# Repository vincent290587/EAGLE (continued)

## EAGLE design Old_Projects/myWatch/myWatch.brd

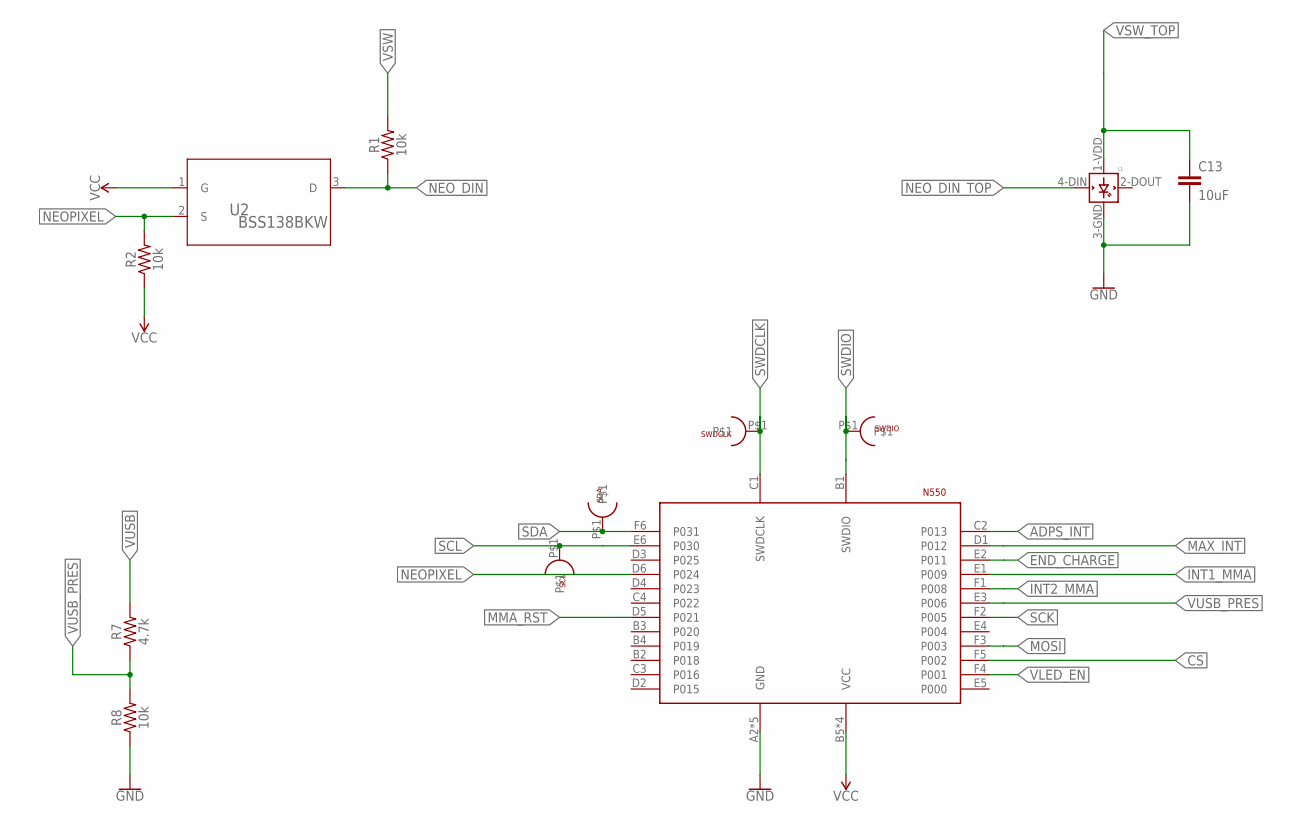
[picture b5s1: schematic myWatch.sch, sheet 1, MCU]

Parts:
C13: 10uF; 0603
L1: WS2812B
R1, R2, R8: 10k; 0603
R7: 4.7k; 0603
SCL: SCL; TESTPOINT
SDA: SDA; TESTPOINT
SWDCLK: TESTPOINT
SWDIO: TESTPOINT
U2: BSS138BKW; SOT65P210X110-3N
U$1: N5150

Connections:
ADPS_INT: U$1.C2 (P013); also elsewhere on the board
CS: U$1.F5 (P002); also elsewhere on the board
END_CHARGE: U$1.E2 (P011); also elsewhere on the board
GND: C13.2, L1.3-GND (GND), R8.1, U$1.A2 (GND), U$1.A3 (GND), U$1.A4 (GND), U$1.A5 (GND), U$1.A6 (GND); also elsewhere on the board
INT1_MMA: U$1.E1 (P009); also elsewhere on the board
INT2_MMA: U$1.F1 (P008); also elsewhere on the board
MAX_INT: U$1.D1 (P012); also elsewhere on the board
MMA_RST: U$1.D5 (P021); also elsewhere on the board
MOSI: U$1.F3 (P003); also elsewhere on the board
NEOPIXEL: R2.2, U2.2 (S), U$1.D6 (P024)
NEO_DIN: R1.1, U2.3 (D); also elsewhere on the board
NEO_DIN_TOP: L1.4-DIN (DIN); also elsewhere on the board
SCK: U$1.F2 (P005); also elsewhere on the board
SCL: SCL.P$1, U$1.E6 (P030); also elsewhere on the board
SDA: SDA.P$1, U$1.F6 (P031); also elsewhere on the board
SWDCLK: SWDCLK.P$1, U$1.C1 (SWDCLK); also elsewhere on the board
SWDIO: SWDIO.P$1, U$1.B1 (SWDIO); also elsewhere on the board
VCC: R2.1, U2.1 (G), U$1.B5 (VCC), U$1.B6 (VCC), U$1.C5 (VCC), U$1.C6 (VCC); also elsewhere on the board
VLED_EN: U$1.F4 (P001); also elsewhere on the board
VSW: R1.2; also elsewhere on the board
VSW_TOP: C13.1, L1.1-VDD (VDD); also elsewhere on the board
VUSB: R7.2; also elsewhere on the board
VUSB_PRES: R7.1, R8.2, U$1.E3 (P006)

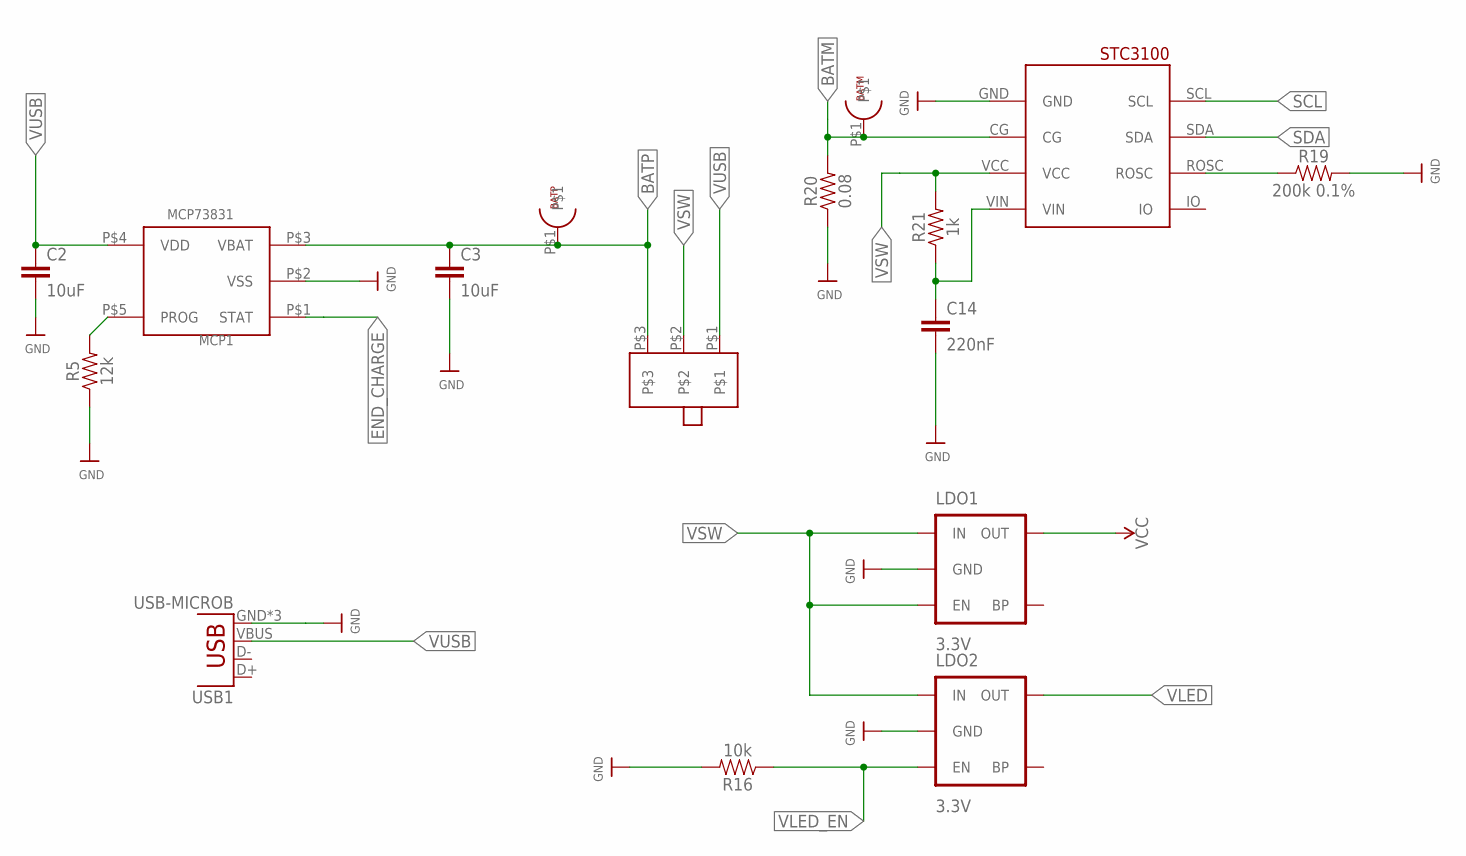
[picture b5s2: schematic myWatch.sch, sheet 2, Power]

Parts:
BATM: BATM; TESTPOINT
BATP: BATP; TESTPOINT
C2, C3: 10uF; 0603
C14: 220nF; 0603
LDO1, LDO2: 3.3V; SOT23-5
MCP1: MCP73831; 5PIN_SOT23
R5: 12k; 0603
R16: 10k; 0603
R19: 200k 0.1%; 0603
R20: 0.08; 0603
R21: 1k; 0603
STC1: STC3100
U$10: JS102011SAQN
USB1: USB-MICROB

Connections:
BATM: BATM.P$1, R20.2, STC1.CG
BATP: BATP.P$1, C3.1, MCP1.P$3 (VBAT), U$10.P$3
END_CHARGE: MCP1.P$1 (STAT); also elsewhere on the board
GND: C2.2, C3.2, C14.2, LDO1.2 (GND), LDO2.2 (GND), MCP1.P$2 (VSS), R5.1, R16.2, R19.2, R20.1, STC1.GND, USB1.GND, USB1.MT1 (GND), USB1.MT2 (GND); also elsewhere on the board
unnamed: MCP1.P$5 (PROG), R5.2
unnamed: R19.1, STC1.ROSC
unnamed: C14.1, R21.1, STC1.VIN
SCL: STC1.SCL; also elsewhere on the board
SDA: STC1.SDA; also elsewhere on the board
VCC: LDO1.5 (OUT); also elsewhere on the board
VLED: LDO2.5 (OUT); also elsewhere on the board
VLED_EN: LDO2.3 (EN), R16.1; also elsewhere on the board
VSW: LDO1.1 (IN), LDO1.3 (EN), LDO2.1 (IN), R21.2, STC1.VCC, U$10.P$2; also elsewhere on the board
VUSB: C2.1, MCP1.P$4 (VDD), U$10.P$1, USB1.VBUS; also elsewhere on the board

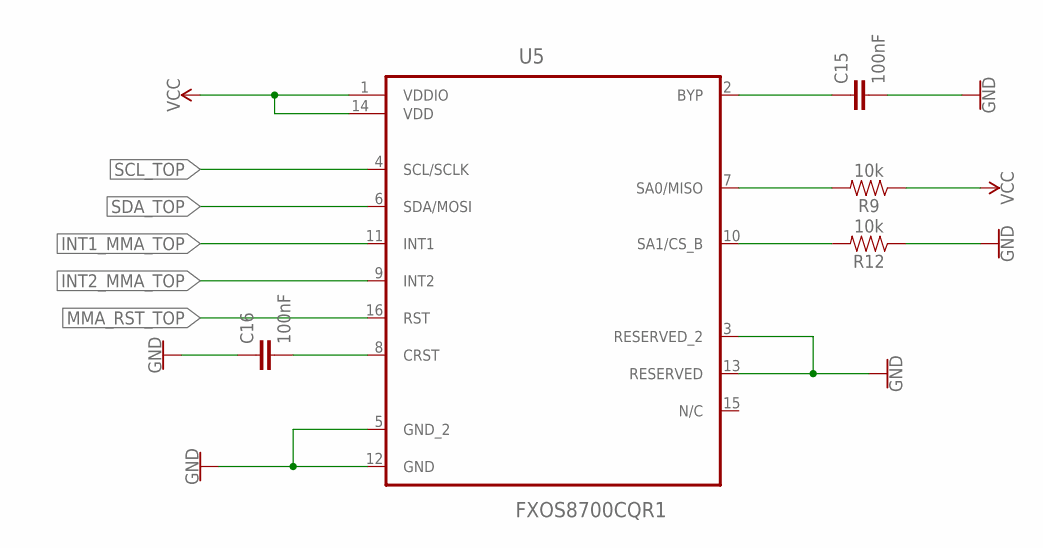
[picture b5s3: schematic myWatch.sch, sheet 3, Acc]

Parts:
C15, C16: 100nF; 0603
R9, R12: 10k; 0603
U5: FXOS8700CQR1; QFN50P300X300X120-16N

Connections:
GND: C15.2, C16.1, R12.1, U5.3 (RESERVED_2), U5.5 (GND_2), U5.12 (GND), U5.13 (RESERVED); also elsewhere on the board
INT1_MMA_TOP: U5.11 (INT1); also elsewhere on the board
INT2_MMA_TOP: U5.9 (INT2); also elsewhere on the board
MMA_RST_TOP: U5.16 (RST); also elsewhere on the board
unnamed: C16.2, U5.8 (CRST)
unnamed: R12.2, U5.10 (SA1/CS_B)
unnamed: R9.2, U5.7 (SA0/MISO)
unnamed: C15.1, U5.2 (BYP)
SCL_TOP: U5.4 (SCL/SCLK); also elsewhere on the board
SDA_TOP: U5.6 (SDA/MOSI); also elsewhere on the board
VCC: R9.1, U5.1 (VDDIO), U5.14 (VDD); also elsewhere on the board

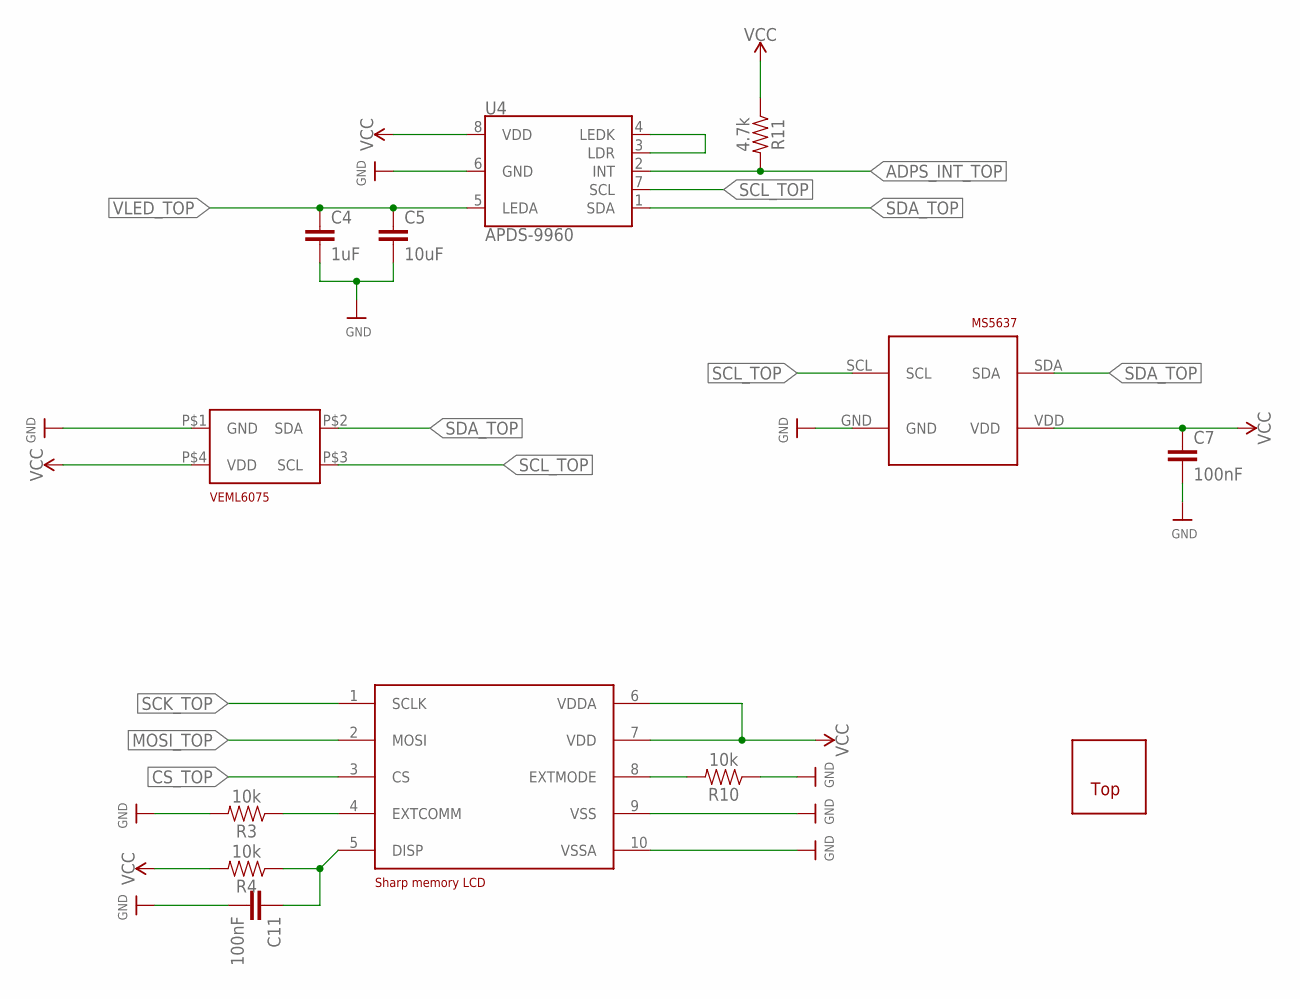
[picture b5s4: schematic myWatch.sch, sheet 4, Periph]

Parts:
C4: 1uF; 0603
C5: 10uF; 0603
C7, C11: 100nF; 0603
MS5637: MS5637
R3, R4, R10: 10k; 0603
R11: 4.7k; 0603
SHARP: SHARP27
U4: APDS-9960
U$2: VEML6075
U$6: WATCH1; WATCH

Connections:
ADPS_INT_TOP: R11.2, U4.2 (INT); also elsewhere on the board
CS_TOP: SHARP.3 (CS); also elsewhere on the board
GND: C4.2, C5.2, C7.2, C11.2, MS5637.GND, R3.2, R10.1, SHARP.9 (VSS), SHARP.10 (VSSA), U4.6 (GND), U$2.P$1 (GND); also elsewhere on the board
MOSI_TOP: SHARP.2 (MOSI); also elsewhere on the board
unnamed: U4.3 (LDR), U4.4 (LEDK)
unnamed: R10.2, SHARP.8 (EXTMODE)
unnamed: R3.1, SHARP.4 (EXTCOMM)
unnamed: C11.1, R4.1, SHARP.5 (DISP)
SCK_TOP: SHARP.1 (SCLK); also elsewhere on the board
SCL_TOP: MS5637.SCL, U4.7 (SCL), U$2.P$3 (SCL); also elsewhere on the board
SDA_TOP: MS5637.SDA, U4.1 (SDA), U$2.P$2 (SDA); also elsewhere on the board
VCC: C7.1, MS5637.VDD, R4.2, R11.1, SHARP.6 (VDDA), SHARP.7 (VDD), U4.8 (VDD), U$2.P$4 (VDD); also elsewhere on the board
VLED_TOP: C4.1, C5.1, U4.5 (LEDA); also elsewhere on the board

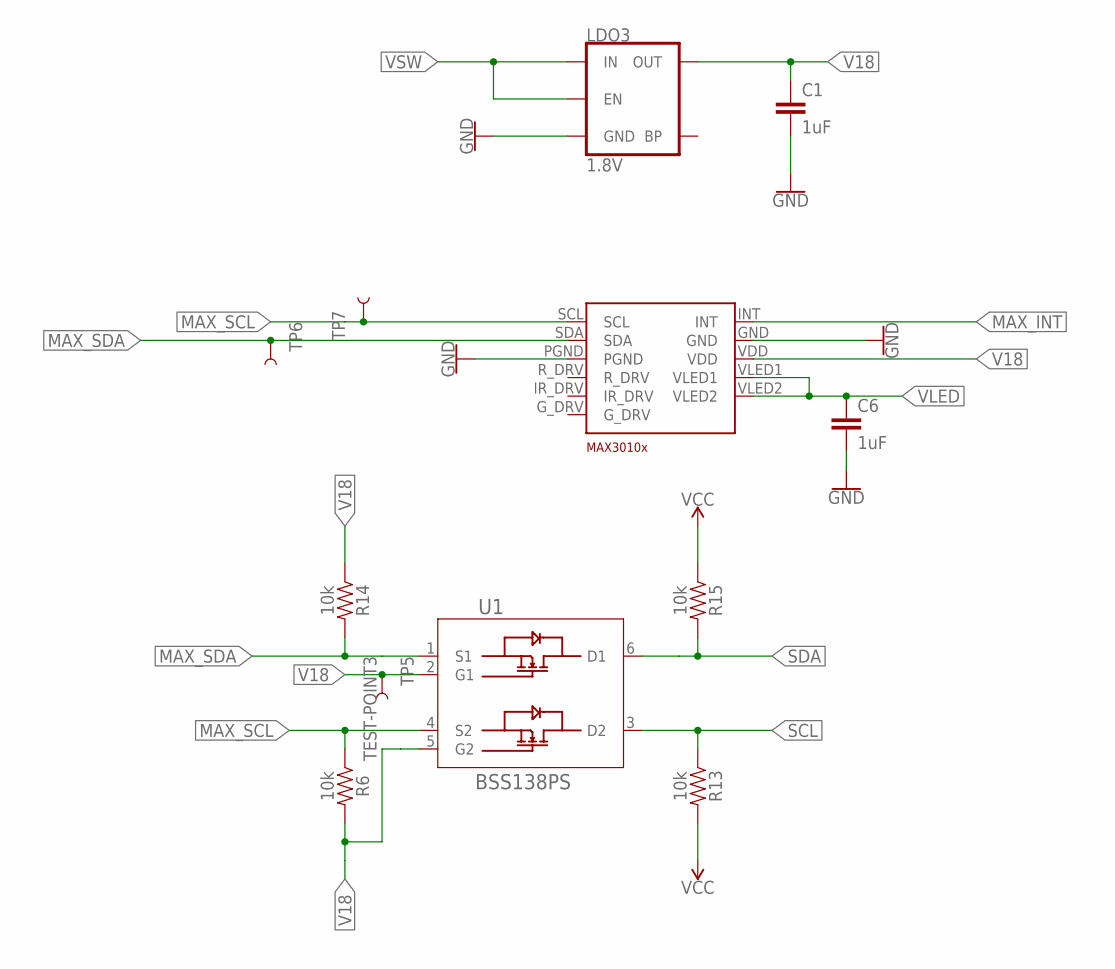
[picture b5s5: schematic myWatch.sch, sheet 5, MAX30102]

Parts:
C1, C6: 1uF; 0603
LDO3: 1.8V; SOT23-5
R6, R13, R14, R15: 10k; 0603
TP5, TP6, TP7: TEST-POINT3; PAD.03X.03
U1: BSS138PS; SOT65P210X110-6N
U3: MAX30102

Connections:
GND: C1.2, C6.2, LDO3.2 (GND), U3.GND, U3.PGND; also elsewhere on the board
MAX_INT: U3.INT; also elsewhere on the board
MAX_SCL: R6.1, TP7.P$1, U1.4 (S2), U3.SCL
MAX_SDA: R14.2, TP6.P$1, U1.1 (S1), U3.SDA
SCL: R13.1, U1.3 (D2); also elsewhere on the board
SDA: R15.2, U1.6 (D1); also elsewhere on the board
V18: C1.1, LDO3.5 (OUT), R6.2, R14.1, TP5.P$1, U1.2 (G1), U1.5 (G2), U3.VDD
VCC: R13.2, R15.1; also elsewhere on the board
VLED: C6.1, U3.VLED1, U3.VLED2; also elsewhere on the board
VSW: LDO3.1 (IN), LDO3.3 (EN); also elsewhere on the board

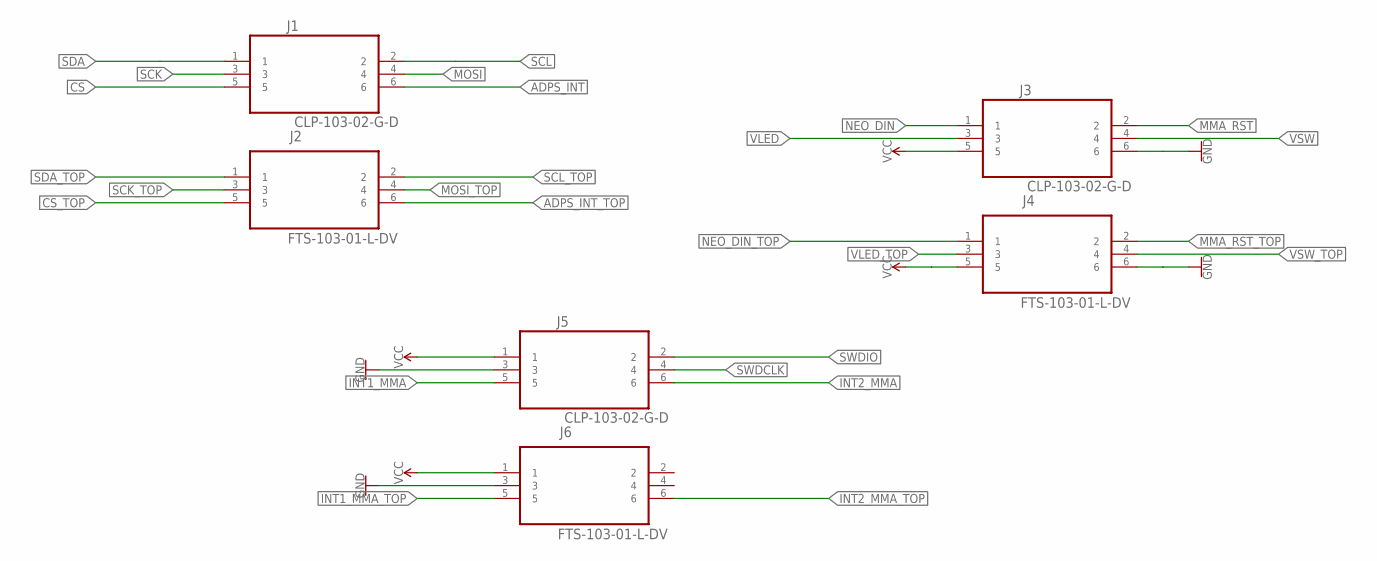
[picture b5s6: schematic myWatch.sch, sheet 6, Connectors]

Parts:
J1, J3, J5: CLP-103-02-G-D; SAMTEC_CLP-103-02-G-D
J2, J4, J6: FTS-103-01-L-DV; SAMTEC_FTS-103-01-L-DV

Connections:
ADPS_INT: J1.6; also elsewhere on the board
ADPS_INT_TOP: J2.6; also elsewhere on the board
CS: J1.5; also elsewhere on the board
CS_TOP: J2.5; also elsewhere on the board
GND: J3.6, J4.6, J5.3, J6.3; also elsewhere on the board
INT1_MMA: J5.5; also elsewhere on the board
INT1_MMA_TOP: J6.5; also elsewhere on the board
INT2_MMA: J5.6; also elsewhere on the board
INT2_MMA_TOP: J6.6; also elsewhere on the board
MMA_RST: J3.2; also elsewhere on the board
MMA_RST_TOP: J4.2; also elsewhere on the board
MOSI: J1.4; also elsewhere on the board
MOSI_TOP: J2.4; also elsewhere on the board
NEO_DIN: J3.1; also elsewhere on the board
NEO_DIN_TOP: J4.1; also elsewhere on the board
SCK: J1.3; also elsewhere on the board
SCK_TOP: J2.3; also elsewhere on the board
SCL: J1.2; also elsewhere on the board
SCL_TOP: J2.2; also elsewhere on the board
SDA: J1.1; also elsewhere on the board
SDA_TOP: J2.1; also elsewhere on the board
SWDCLK: J5.4; also elsewhere on the board
SWDIO: J5.2; also elsewhere on the board
VCC: J3.5, J4.5, J5.1, J6.1; also elsewhere on the board
VLED: J3.3; also elsewhere on the board
VLED_TOP: J4.3; also elsewhere on the board
VSW: J3.4; also elsewhere on the board
VSW_TOP: J4.4; also elsewhere on the board

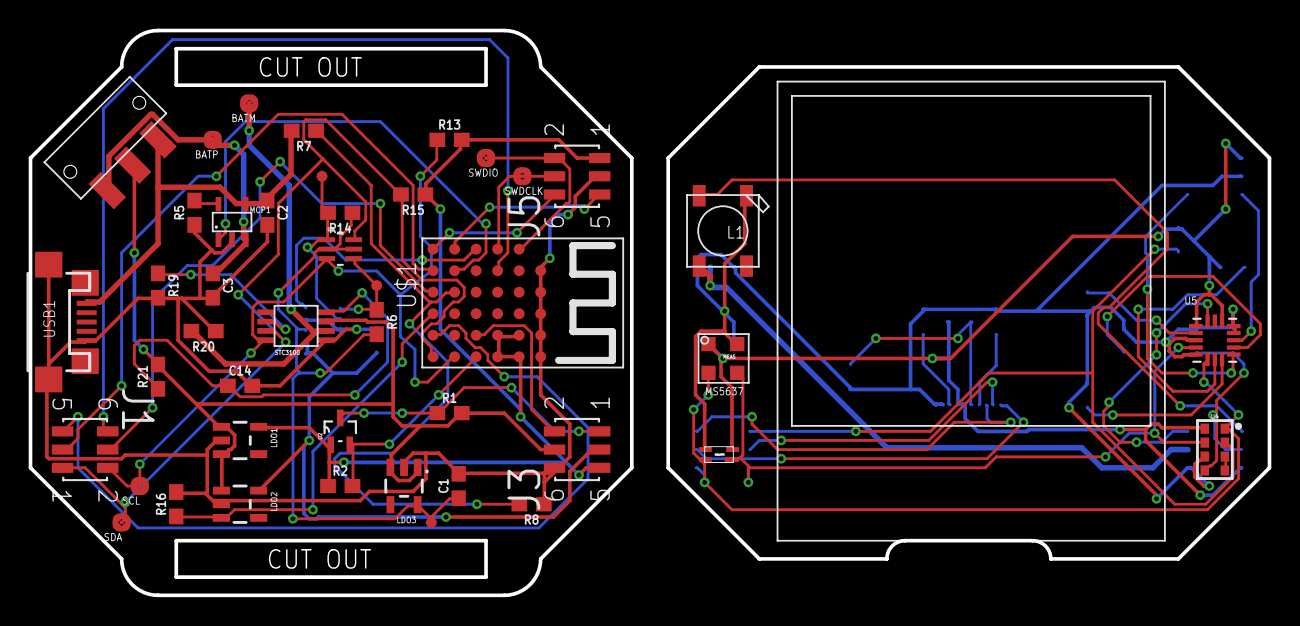
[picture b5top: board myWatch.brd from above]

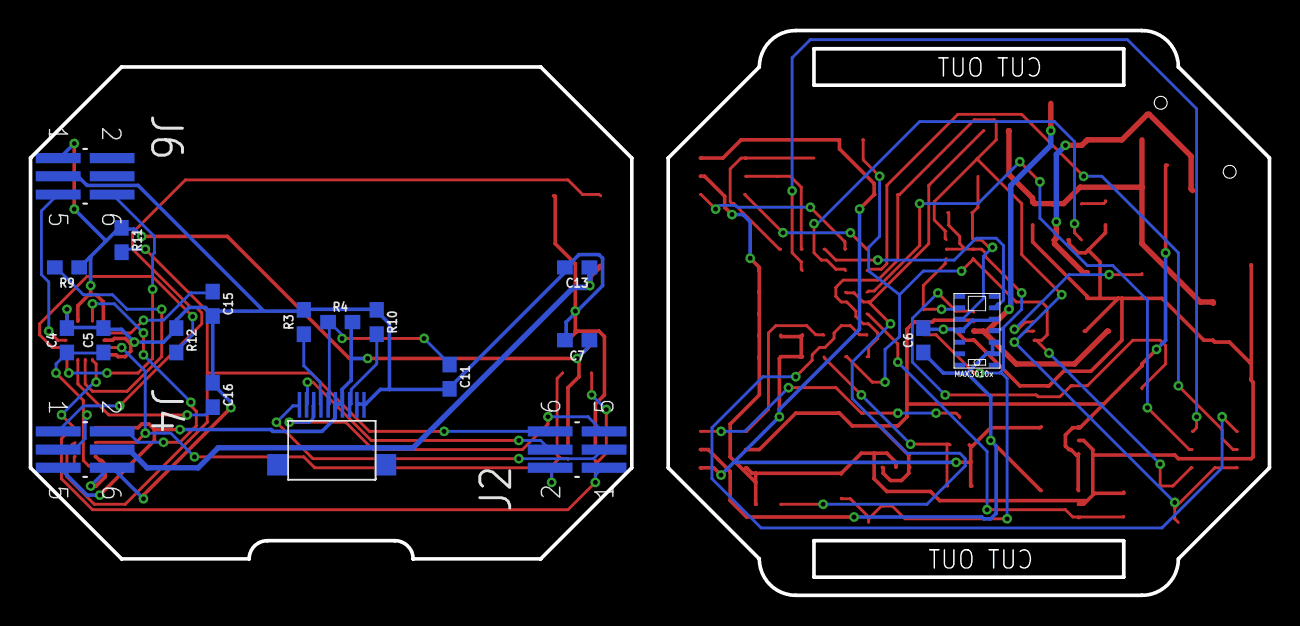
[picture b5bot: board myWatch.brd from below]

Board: 2 copper layers, 86.4 x 39.4 mm, 64 parts (20 on the bottom side), 50 nets.

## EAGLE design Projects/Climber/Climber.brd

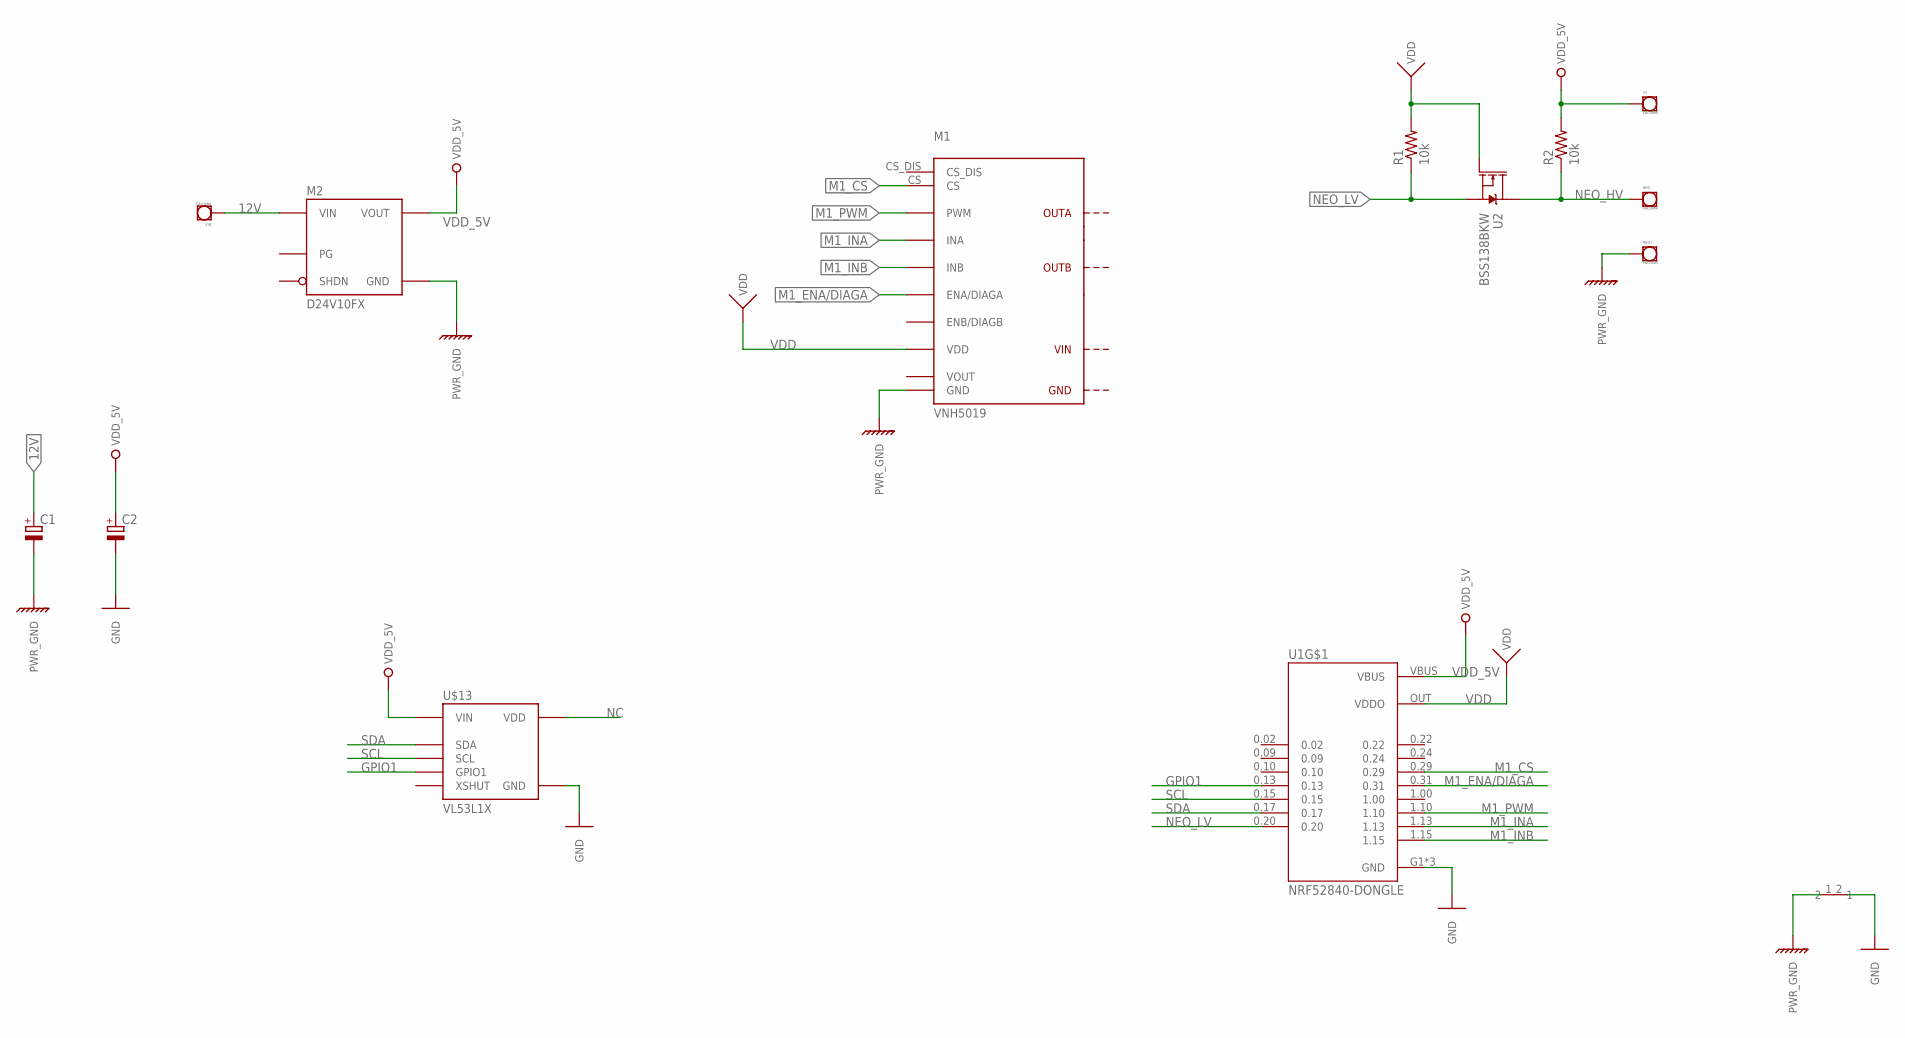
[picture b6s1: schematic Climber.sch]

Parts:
5V: PAD3MM; PAD_3
C1, C2: CPOL-EUE5-4; E5-4
M1: VNH5019
M2: D24V10FX
NEO, NEO1: PAD3MM; PAD_3
R1, R2: 10k; R0603
U1: NRF52840-DONGLE; MODULE_NRF52840-DONGLE
U2: BSS138BKW; SOT65P210X110-3N
U$10: NET_CONN
U$13: VL53L1X
VIN: PAD3MM; PAD_3

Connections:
12V: C1.+, M2.VIN, VIN.P$1
GND: C2.-, U1.G1 (GND), U1.G2 (GND), U1.G3 (GND), U$10.2, U$13.GND
GPIO1: U1.0.13, U$13.GPIO1
M1_CS: M1.CS, U1.0.29
M1_ENA/DIAGA: M1.ENA (ENA/DIAGA), U1.0.31
M1_INA: M1.INA, U1.1.13
M1_INB: M1.INB, U1.1.15
M1_PWM: M1.PWM, U1.1.10
NC: U$13.VDD
NEO_HV: NEO.P$1, R2.1, U2.3 (D)
NEO_LV: R1.1, U1.0.20, U2.2 (S)
PWR_GND: C1.-, M1.GND@0 (GND), M1.GND@1 (GND), M2.GND, NEO1.P$1, U$10.1
SCL: U1.0.15, U$13.SCL
SDA: U1.0.17, U$13.SDA
VDD: M1.VDD, R1.2, U1.OUT (VDDO), U2.1 (G)
VDD_5V: 5V.P$1, C2.+, M2.VOUT, R2.2, U1.VBUS, U$13.VIN
VOUT: M1.VOUT

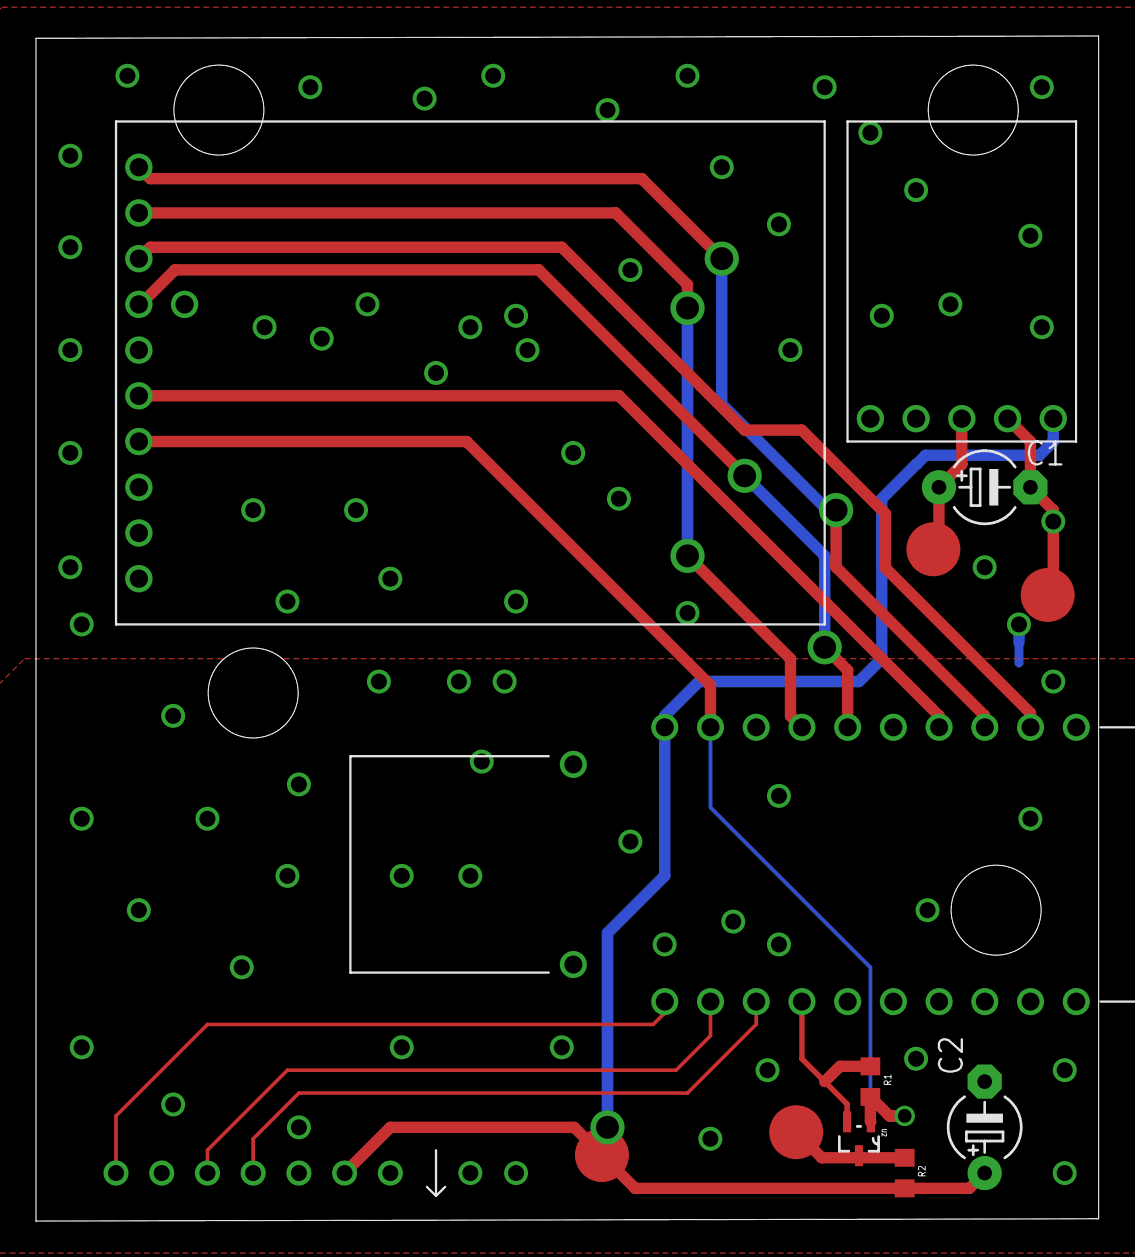
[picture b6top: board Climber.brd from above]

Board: 2 copper layers, 59.0 x 65.8 mm, 14 parts (1 on the bottom side), 15 nets.

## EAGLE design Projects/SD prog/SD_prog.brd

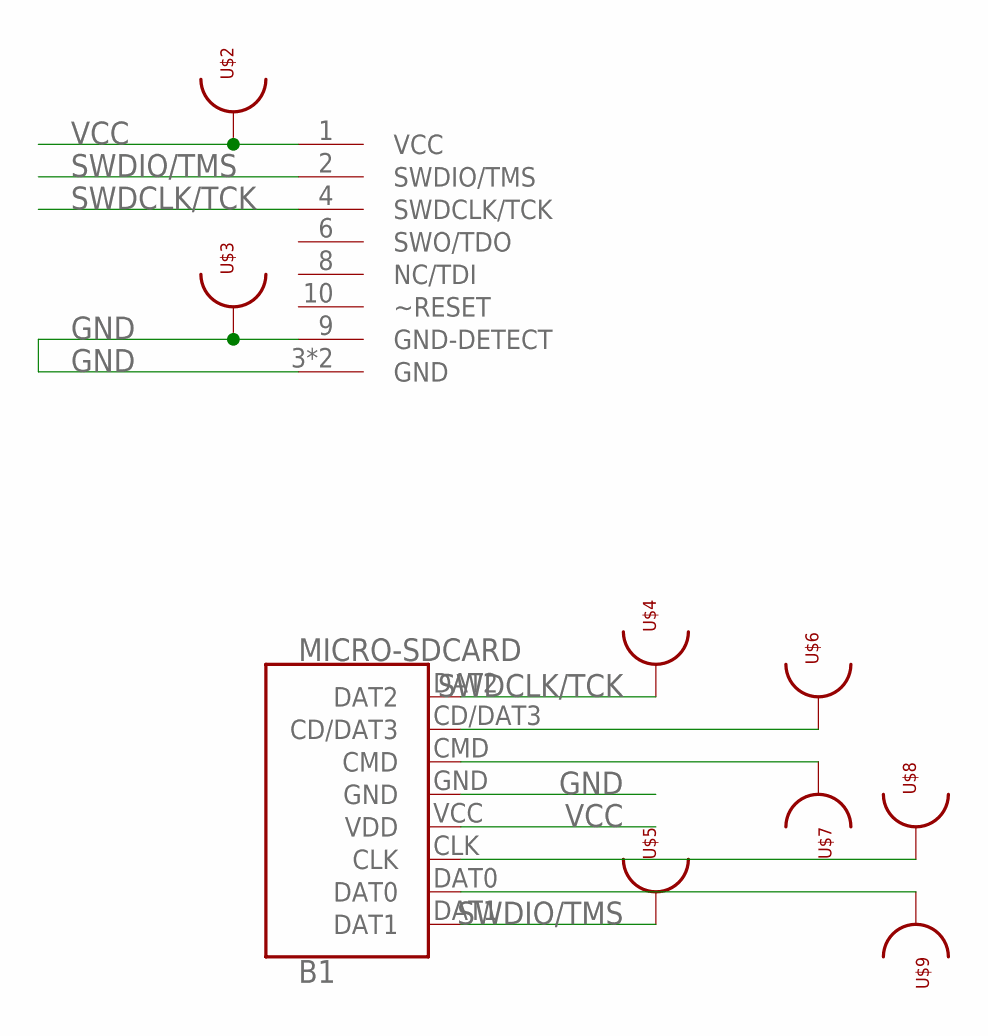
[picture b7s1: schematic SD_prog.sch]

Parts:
B1: MICRO-SDCARD
U$1: 2X5_0.05"_CORTEX_DEBUGTH_NOKEY_UNSHROUDED; 2X5_0.05"_TH_NS
U$2, U$3, U$4, U$5: TESTPOINT_33
U$6, U$7, U$8, U$9: TESTPOINT_22

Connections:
GND: B1.GND, U$1.3 (GND), U$1.5 (GND), U$1.9 (GND-DETECT), U$3.P$1
unnamed: B1.CD/DAT3, U$6.P$1
unnamed: B1.CMD, U$7.P$1
unnamed: B1.CLK, U$8.P$1
unnamed: B1.DAT0, U$9.P$1
SWDCLK/TCK: B1.DAT2, U$1.4 (SWDCLK/TCK), U$4.P$1
SWDIO/TMS: B1.DAT1, U$1.2 (SWDIO/TMS), U$5.P$1
VCC: B1.VCC (VDD), U$1.1 (VCC), U$2.P$1

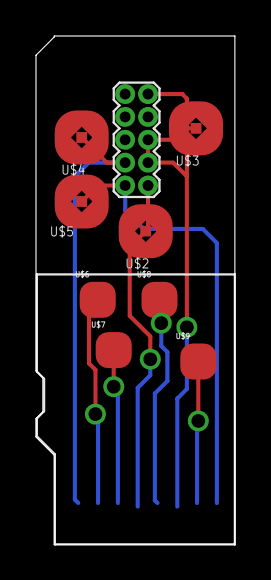
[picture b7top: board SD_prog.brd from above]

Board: 2 copper layers, 11.0 x 28.2 mm, 10 parts (1 on the bottom side), 8 nets.

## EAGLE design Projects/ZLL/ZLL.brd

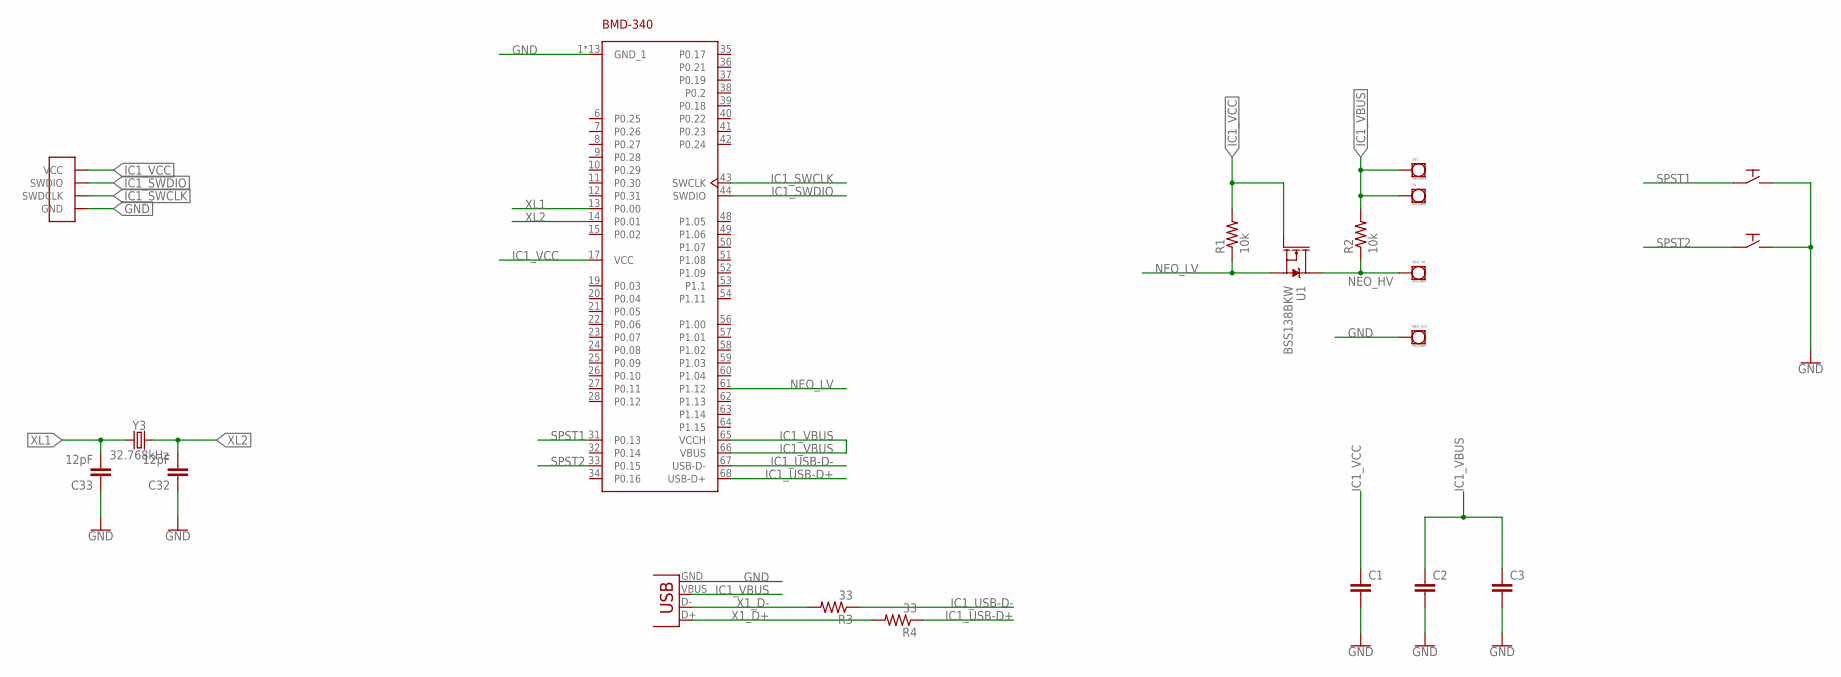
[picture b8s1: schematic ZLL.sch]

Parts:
5V, 5V1: PAD3MM; PAD_3
C1, C3: C-EUC0603; C0603
C2: C-EUC0805; C0805
C32, C33: 12pF; C0603
IC1: BMD-340-A-R; BMD340AR
NEO_HV, NEO_HV1: PAD3MM; PAD_3
R1, R2: 10k; R0603
R3, R4: 33; R0603
SPST1, SPST2: PTS526SK08; PTS526SKG15SMTR2LFS
U1: BSS138BKW; SOT65P210X110-3N
U$1: PROG_SMD
X1: USB-MICROB
Y3: 32.768kHz; CRYSTAL-SMD-3.2X1.5MM

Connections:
GND: C1.2, C2.2, C3.2, C32.1, C33.1, IC1.1 (GND_1), IC1.2 (GND_1), IC1.3 (GND_1), IC1.4 (GND_1), IC1.5 (GND_1), IC1.16 (GND_1), IC1.18 (GND_1), IC1.29 (GND_1), IC1.30 (GND_1), IC1.45 (GND_1), IC1.46 (GND_1), IC1.47 (GND_1), IC1.55 (GND_1), NEO_HV1.P$1, SPST1.3, SPST1.4, SPST2.3, SPST2.4, U$1.GND, X1.GND
IC1_SWCLK: IC1.43 (SWCLK), U$1.PIN1 (SWDCLK)
IC1_SWDIO: IC1.44 (SWDIO), U$1.PIN2 (SWDIO)
IC1_USB-D+: IC1.68 (USB-D+), R4.1
IC1_USB-D-: IC1.67 (USB-D-), R3.1
IC1_VBUS: 5V.P$1, 5V1.P$1, C2.1, C3.1, IC1.65 (VCCH), IC1.66 (VBUS), R2.2, X1.VBUS
IC1_VCC: C1.1, IC1.17 (VCC), R1.2, U1.1 (G), U$1.VCC
NEO_HV: NEO_HV.P$1, R2.1, U1.3 (D)
NEO_LV: IC1.61 (P1.12), R1.1, U1.2 (S)
SPST1: IC1.31 (P0.13), SPST1.1, SPST1.2
SPST2: IC1.33 (P0.15), SPST2.1, SPST2.2
X1_D+: R4.2, X1.D+
X1_D-: R3.2, X1.D-
XL1: C33.2, IC1.13 (P0.00), Y3.P$1 (1)
XL2: C32.2, IC1.14 (P0.01), Y3.P$2 (2)

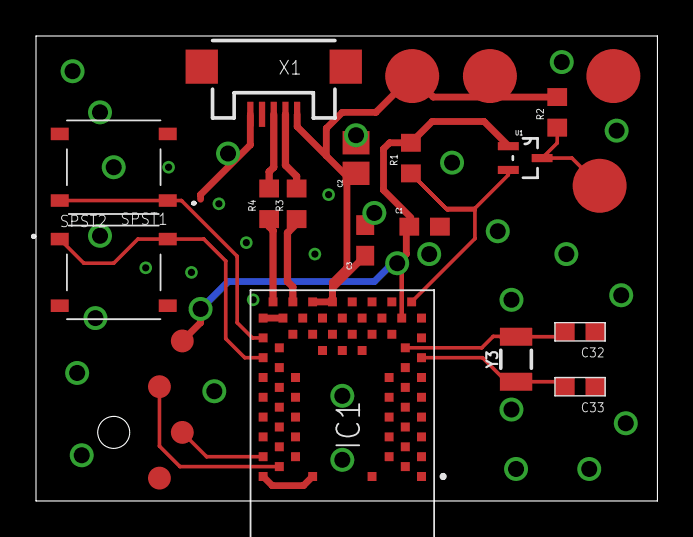
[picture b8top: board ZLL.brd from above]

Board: 2 copper layers, 34.5 x 25.8 mm, 20 parts (0 on the bottom side), 15 nets.

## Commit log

2015-11-07 Commit initial
2016-05-01 Ajout de STC3100
2016-05-14 Correction de ANTAP28 & ajout du nouveau D52Q
2016-06-04 Ajout du barometre MS5637
2017-06-11 nrf52840 addition
2017-06-11 Create README.md
    Added nrf52840
2017-06-12 Addition of multiple files
2017-08-24 Shortened distance between pins and pads
2017-08-24 Added gitignore
2017-08-24 Missing libraries
2017-09-16 MK20 info layer update Replaced USB milling with holes
2017-12-21 Added: - a FPC Molex 12 0.5mm connector - Attiny816 / Attiny817 footprints
2018-05-26 New libraries
2018-05-30 Addition of GPS lib Modification of USB lib
2018-05-30 Addition of libraries
2018-05-30 Added library loader part
2018-06-01 Moved all libraries to new folder
2018-06-01 Changed SamacSys library location
2018-06-01 Added DRU folder
2018-06-01 Finished board
2018-06-01 SMD programming interface
2018-06-01 Pogo programming board sketch
2018-06-01 Added CAM processors
2018-06-03 Final design
2018-06-04 Added speaker
2018-06-21 Some fuckups corrected
2018-06-21 Added one more pogo pin
2018-06-21 Updated nRF52840
2018-06-21 Changed packages Routed USB_PRES
2018-06-28 Corrected mistakes on myStravaV10
2018-08-08 New amplifier project
2018-08-08 Created schematic and first placement
2018-08-09 Added attributes and MPN Created the power circuit
2018-08-10 Updated power xfer
2018-08-29 Created library for audio transformer
2018-09-03 Added library for audio caps
2018-09-04 Cleanup and schematic for the amplifier part
2018-11-05 Improved version of the bike GPS
2018-11-08 Board routed completely:to be checked
2018-11-08 Added small capacitors More vias
2018-12-12 Updated nRF52840 footprint
2018-12-13 Added the strava V3, with Rigado module
2019-01-10 Replaced barometer in strava V3
2019-01-18 DapLink commit
2019-01-22 Corrected BMD340 footprint Update the board with FRAM, bme280 and new pins assignments
2019-01-24 Thermal routing for BMD340
2019-01-24 Thermals added
2019-03-23 New cadence & power sensor
2019-03-23 New libraries Board routing started
2020-01-04 Added Zwift commander !
2020-02-11 Added Climber PCB and libs
2020-02-12 New devices in Climber
2020-02-12 Added ZLL PCB, finished climber PCB
2020-02-13 More on the nRF51 USB key
2020-02-13 Added PCB SD card symbol
2020-02-13 ZwiftCommand with nRF52
2020-02-13 Strava V3 FRAM value set
2020-02-13 Added FRAM lib
2020-02-13 Corrected SD card library
2020-02-15 Added buttons on ZLL Added pads on nRF51 key SD prog finished N5 lib updated
2020-02-26 nRF51 dongle with new pins
2020-02-26 Simplified strava
2020-02-27 Updated 5V boost DCDC converter
2020-02-28 Updated stravaV3 Updated Climber
2020-02-29 Order @ Boktech
2020-04-20 Added myWatch project
2020-10-04 Massive library update Added projects Added 3D packages
2020-10-05 Added stuff on RingerPro
2020-10-21 RingerPro update
2020-11-11 Added RingerPro2 Added new barometer BPM390 Added LTC3105
